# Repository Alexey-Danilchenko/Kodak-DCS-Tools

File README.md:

# Firmwares, Tools and sources to explore Kodak DCS cameras

This project contain the sources of all the tools produced as a result of my explorations of Kodak's DCS cameras: their internals, firmware, sensors, remaps, profile extraction etc. Quite a few of the tools are in aid of reverse engineering the firmwares and others are the results of those explorations.

I have mostly concentrated on Kodak ProBack 645M/C/H and SLRs Kodak DCS 14n, SLR/n, SLR/c models but a few of the tools are generic enough and may be applicable to other DCS cameras or standalone.

All software on this site is released free and under GPL license and in hope that it will be useful to other reverse engineers and Kodak camera explorers and users. 

The following is the list of topics:

* [Firmwares for Kodak cameras that I have build](Firmwares)
* [Camera profiles and profile extraction for Kodak cameras](profiles.md)
* [Software utilities (compiled versions of the sources above)](tools.md)
* [Mamiya/Phase One camera to digital back communication protocol](Mamiya_Protocol)
* [All the source code (defective pixels remap tools, IDA plugins, profile extraction, etc)](sources)
* [Sources of some of the code that I reverse engineered from firmwares and DSP](Firmwares/Reversed_Sources)
* [Kodak ProBack 645M/C/H hardware info - viewfinder masks, IR filters etc](hardware.md)
* [ProBack LCD upgrade to LED backlighting - daylight visible](Hardware/ProBack_LED_backlight)

The details of some of these explorations are published [here](https://dalex-257.livejournal.com/).

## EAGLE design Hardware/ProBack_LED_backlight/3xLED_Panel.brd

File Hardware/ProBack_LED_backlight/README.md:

# ProBack screen upgrade to use LED backlighting

Proback is an old digital back using [Sanyo ALP230CCX LCD](Ref/ALP230CCX.pdf) with CCFL tube as backlighting (that was a technology back in 2001). The CCFL tube lights up the edge of the screen and light guide plate with diffusers and light boosting sheets providing a backlight. The backlighting achieved this way is ok to start with but as CCFL tube ages it gets very weak and in a strong daylight practically nothing can be seen on the LCD. Besides CCFL tubes have limited lifespan and cannot be replaced since it is hard to find the sourcereplacemnt of that size nowadays. The aim of this hardware project is a complete replacement of this backlighting system with LED board instead of CCFL tube driven from the same on/off signal as the main backlight. The goal of it is to make it more usable in direct sunlight. This is the end result:

## Project history

This project followed the footsteps of something similar already done [here (link in russian)](https://web.archive.org/web/20171017015512/http://wowcamera.info/viewtopic.php?f=18&t=815&sid=7ef8761ab0095eecd0e935a0096e5fdd&start=740) but does a properly designed LED light source with constant current control.

I have designed the LED boards originally for 3x SMD LEDs in 2835 packages to fit perefecly inside LCD outer casing instead of CCFL. However upon experimenting with that it appears that Sanyo LCD backlight construction uses a light guide plate with straight vertical pattern that may work with linear light source like CCFL tube but does not work well with just a few LEDs creating long vertical beams of light. Modern LCD light guide panels use diaginal pattern that scatter light more evenly. With this in mind I also designed board for 6x SMD LEDs more closely spaced - those will need to be driven at close to a half the rated current to have the same power usage and light output as the 3x LEDs.

The alternative to 6x LED board and direct replacement is to place 3x LED lights sideways to the edge of the light guide - that means the light source needs to be behind the LCD case and holes for the LEDs need to be drilled into metallic frame to allow this ([similar to this](https://web.archive.org/web/20171021101310if_/http://wowcamera.info/download/file.php?id=11161&sid=97ba8f0b739cfa263edd7aab8cd7707e) used in approach from the russian project linked above). The latter approach is more involved than simple drop-in light replacement as this whole LED boards were designed to be but may be better at providing more uniform lighting.

The LED driver board provides constant current source from 3.3V and can be adjusted for your LEDs (by calculating R2 values for your LEDs current and is R2 = 95 mV / LED current mA (also see a note on schematic with a few sample values). The driver board was intentionally designed to be very small to fit onto a free space on ProBack board close to LCD and backlight power source.

Current design was tested with Yuji LEDs [YJ-BC-2835L](https://www.yujiintl.com/bc-2835l-0-2w/) (20-24 lumens per LED at rated current - CRI95). You can also use any other LEDs in 2835 packaging - make sure they have low forward voltage (<3.3V) and not a very high current (typically around 60mA for CRI95). The [Lumileds White CRI95 LED](https://eu.mouser.com/ProductDetail/Lumileds/L128-5095HA35000B1?qs=W%2FMpXkg%252BdQ4dqd7YM%2FLVnw%3D%3D) (manufacturer part number L128-5095HA35000B1) seems to be an ideal exact alternative to Yuji LEDs that is widely available (hence it is also specified below in list of parts as alternative).

This is assembled driver and LED light source for 3x LEDs designed to go behind LCD frame:

This is assembled driver and LED light source look for 6x LEDs designed to go in place as direct replacement of CCFL tube:

And this is 6x LED light source installed in place of CCFL and powered with LCD off - this shows drawback of this type of lighting caused by the linear structure of light guide panel. It could be addressed by sourcing the replacement for light guide panel with diagonal etching pattern but I have not managed to find any suitable replacement just yet.

Even with the visible backlight pattern, this is far easier to install since it is essentially taking CCFL tube out and placing LED strip board in its place and requires no drilling and no modifications of LCD frame. The brightness here on photo was reduced in postprocessing to show the pattern - in reality the backlight is much brighter.

For the Yuji LEDs above, the board in examples uses regulated LED current of 35mA (with resistor values as selected in schematics and specified in parts list below). For a string of 6 LEDs it produces voltage of 17V (slightly less but that is highly dependent on LED variations). This gives overall power consumption of 595mW which is still slightly less than original CCFL light at 600mW yet it is substantially brighter.

For the 6x LED board of the Yuji LEDs above, I would not recommend to go for brighter than with LED current of 35mA (30..35mA is the ideal range) since it then gets too bright and beyond capabilities of the LCD itself to handle (black becomes too bright). So the resistor values in the list of parts section below reflect this. I personally ended up using 35mA current and it is just about right balance.

This is how it looks all connected and lit:

## What is provided

In this repository you can find Eagle CAD [schematics](LED_Driver_Separate.sch) and [board](LED_Driver_Separate.brd) for LED driver, [schematics](3xLED_Panel.sch) and [board](3xLED_Panel.brd) for 3x LED board and [schematics](6xLED_Panel.sch) and [board](6xLED_Panel.brd) for 6x LED board. I have tested both LED boards but ended up using 6x one as it required no modification to LCD assembly and is more compact.

Separately you can also find [list of parts](BOM.csv) as well.

Gerber files for all the boards are in [Gerbers](Gerbers) subfirectory and are produced for [PCBWay](https://www.pcbway.com/) specifications (they were the only ones I found who can produce LED boards at 3mm minimum width).

When ordering the boards, LED lights board should be finished in white and have a thickness of 1.6mm - this ensures precise fit into a frame and sitting very close to the light guide panel. Minimal board width in PCBWay is 3mm and it is exact size of the gap in LED aluminium frame - so the fit is very tight. I would recommend to file boards a bit to 2.9mm for slightly easier fit.

The driver board for aesthetic reason should be green (to match the main board) and be any thickness of up to 1.6mm - ideally I would choose 0.8mm.

## LCD disassembly and light replacement

LCD assembly in a metal frame is a sandwich consisting of LCD panel itself (1), light boosting sheet of material under it (2), then diffusion sheet of material (3), then light guide acrylic panel (4) with white reflective material behind it and CCFL tube on one of the sides. All of that is packed within a metal frame.

It is relatively straightforward to take apart - LCD panel could be pried apart from the frame via side slots with a small screwdriver. This is how it looks when it is taken away:

Take a note of the corner pointed to by red arrow - the light boosting sheet and diffusing sheet have one rounded corner that goes in only one way in the right bottom corner of the LCD assembly. Next, gently take away light boosting sheet (it has metal sheen on one side):

Then, gently take away diffusion sheet, again noting round corner and where it should go:

All the components here are numbered with their order in the assembly from the top starting with LCD panel.

Lastly, take the light guide assembly from the frame, peel off the CCFL tube with the little white reflective sleeve holding it and discard the tube. Cut off the parts of white sleeve that stick to the light guide panel, both top and bottom bits and stick them both back to the light guide panel (this is important to avoid light bleeds). See the photo above where sleeve was already cut off and both parts were put back on with indication of the top part.

Next, push the LCD light board into the metal frame (it should be pretty tight) as far as it can go:

After that, place all the components back in the reverse order: light guide panel (4), then diffusion sheet (3) noting round corner position, then light boosting sheet (2) noting round corner position and at last put in the LCD panel (1) and click it into place. The LCD assembly is now complete.

## Board attachment

The LED driver board is designed to go on the empty space of the last board connecting to LCD - that sits directly behind CF card slot in the assembled position. Solder two short insulated wires to LED driver board, postion it close to C15 and C21 capacitors and solder ground and + wires as shown on this photo:

Both C15 and C21 are connected in parallel so it really does not matter which one of them the wires are soldered to, but the sides of them: top one for GND and lower side for +3.3V. When soldered, plug in ProBack battery briefly to check backlight working. Then glue the LED driver board to the ProBack board. I used Sugru to attach the board to the main board and insulate the contacts (this is mainly to be able to detach the driver board should I ever need to replace it):

Then attach the LCD connector and put the LCD in place with the ProBack board on top. For added safety, loosely cover LED driver board by Capton tape:

Then assemble the ProBack and test it on camera in the field.

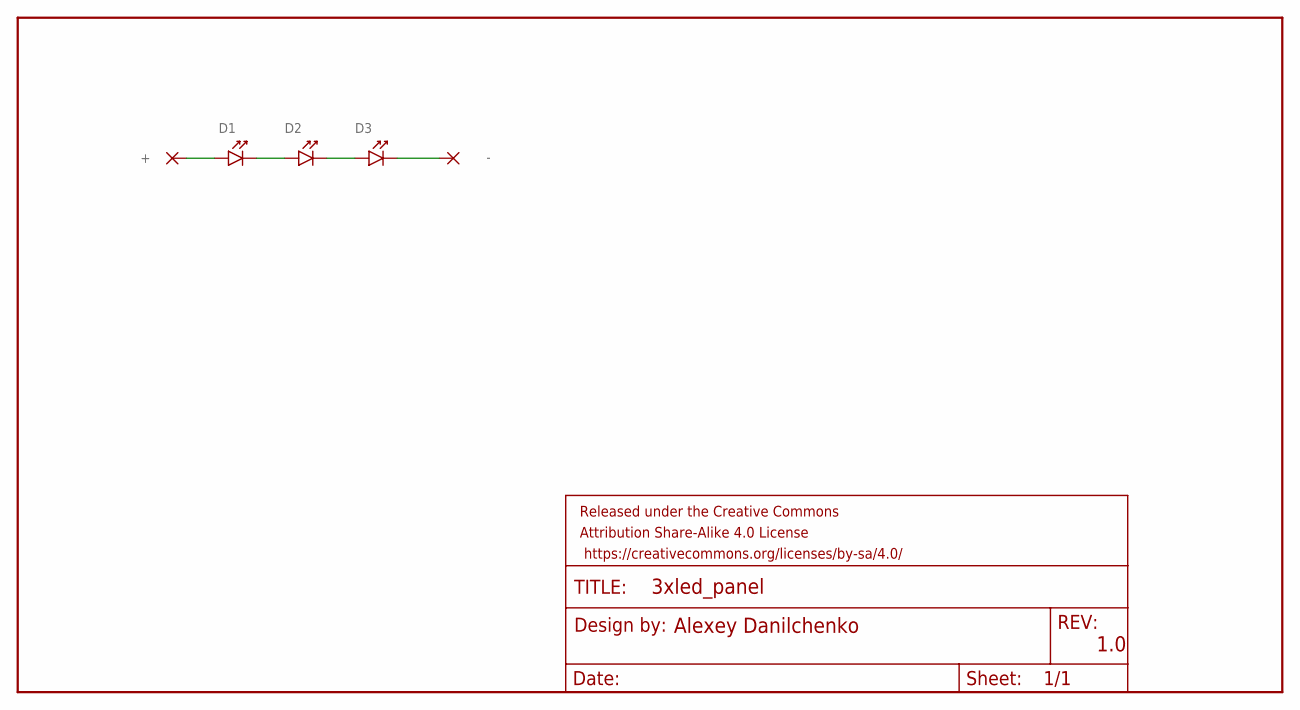
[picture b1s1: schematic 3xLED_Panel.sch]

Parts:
+: WIREPAD1,6/0,9; SMD3-2,15
-: SMD3X2.15; SMD3-2,15
D1, D2, D3: YUJI_2835_SMD; 2835_SMD
FRAME1: FRAME-LEDGER; CREATIVE_COMMONS

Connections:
unnamed: D1.CATHODE, D2.ANODE
unnamed: +.1, D1.ANODE
unnamed: D2.CATHODE, D3.ANODE
unnamed: -.1, D3.CATHODE

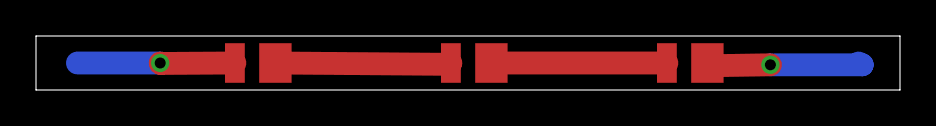
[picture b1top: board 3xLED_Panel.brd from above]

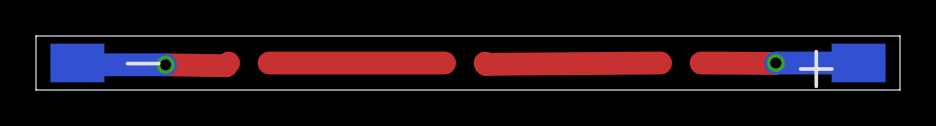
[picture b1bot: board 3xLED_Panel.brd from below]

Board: 2 copper layers, 48.0 x 3.0 mm, 6 parts (2 on the bottom side), 4 nets.

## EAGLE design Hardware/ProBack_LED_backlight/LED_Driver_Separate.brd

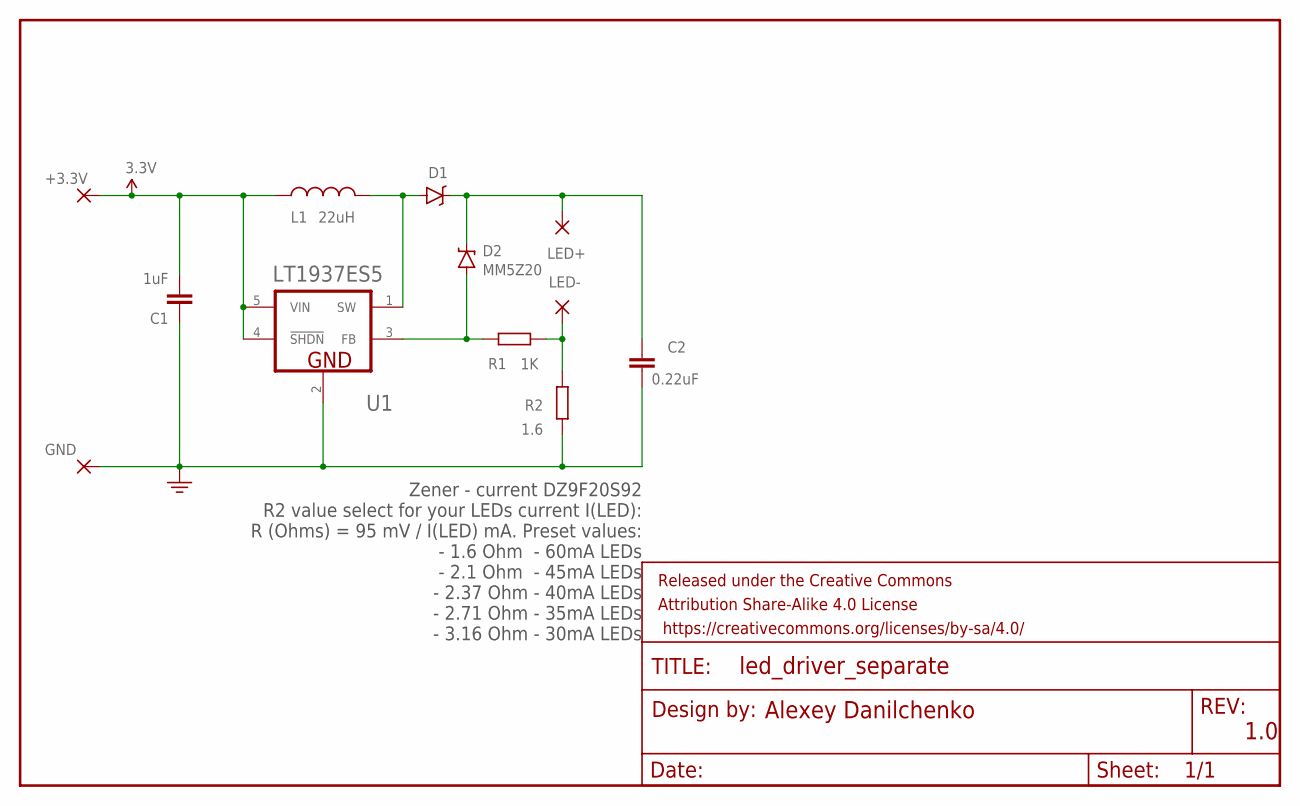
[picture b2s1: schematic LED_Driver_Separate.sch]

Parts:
+3.3V: SMD2X2; SMD2,54-2,54
C1: 1uF; C0805
C2: 0.22uF; 0603-CAP
D1: RB751; SOD-523
D2: MM5Z20; SOD-523
FRAME1: FRAME-LEDGER; CREATIVE_COMMONS
GND: SMD2X2; SMD2,54-2,54
L1: 22uH; 1210
LED+: SMD2X2; SMD2,54-2,54
LED-: SMD2X2; SMD2,54-2,54
R1: 1K; R0805
R2: 1.6; M1206
U1: LT1937ES5; LINEAR_TECHNOLOGY_LT1937ES5#TRMPBF_1

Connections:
3.3V: +3.3V.1, C1.1, L1.1, U1.4 (!SHDN!), U1.5 (VIN)
GND: C1.2, C2.2, GND.1, R2.1, U1.2 (GND)
unnamed: D1.A, L1.2, U1.1 (SW)
unnamed: D2.A, R1.2, U1.3 (FB)
unnamed: LED-.1, R1.1, R2.2
unnamed: C2.1, D1.C, D2.C, LED+.1

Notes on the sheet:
Zener - current DZ9F20S92 R2 value select for your LEDs current I(LED): R (Ohms) = 95 mV / I(LED) mA. Preset values: - 1.6 Ohm - 60mA LEDs - 2.1 Ohm - 45mA LEDs - 2.37 Ohm - 40mA LEDs - 2.71 Ohm - 35mA LEDs - 3.16 Ohm - 30mA LEDs
MM5Z20

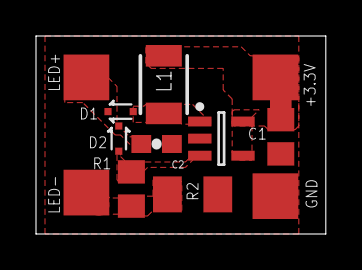
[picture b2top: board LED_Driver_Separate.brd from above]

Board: 2 copper layers, 16.1 x 11.0 mm, 13 parts (0 on the bottom side), 6 nets.

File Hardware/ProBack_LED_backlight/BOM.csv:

Part,Value,Package,Description,"Manufacturer product number, MPN",Manufacturer
C1,1uF,0805,"Capacitor X7R, 50V",CL21B105KBFNNNE,Samsung Electro-Mechanics
C2,0.22uF,0603,"Capacitor X7R, 50V",GCM188R71H224KA64D,Murata Electronics
D1,,SOD-523,Schottky diode,RB521S30T1G,ONSEMI
D2,,SOD-523,"Zener Diode, 20V, >0.1mA",BZT585B20T-7,Diodes Incorporated
L1,22uH,1210,Inductors,LQH32CN220K53L,Murata Electronics
R1,1K,0805,"Resistor, 1%",CRCW08051K00FKEA,Vishay Dale
R2,2.67,1206,High precision 0.1% resistor,CPF1206B2R67E1,TE Connectivity Passive Product
U1,,TSOT-23-5,"LED regulator from LT, TSOT-23 5pin package",LT1937ES5#TRMPBF,Linear Technologies
LEDS,,2835,YUJILEDS high CRI 2835 SMD,YJ-BC-2835L-G02,YUJILEDS

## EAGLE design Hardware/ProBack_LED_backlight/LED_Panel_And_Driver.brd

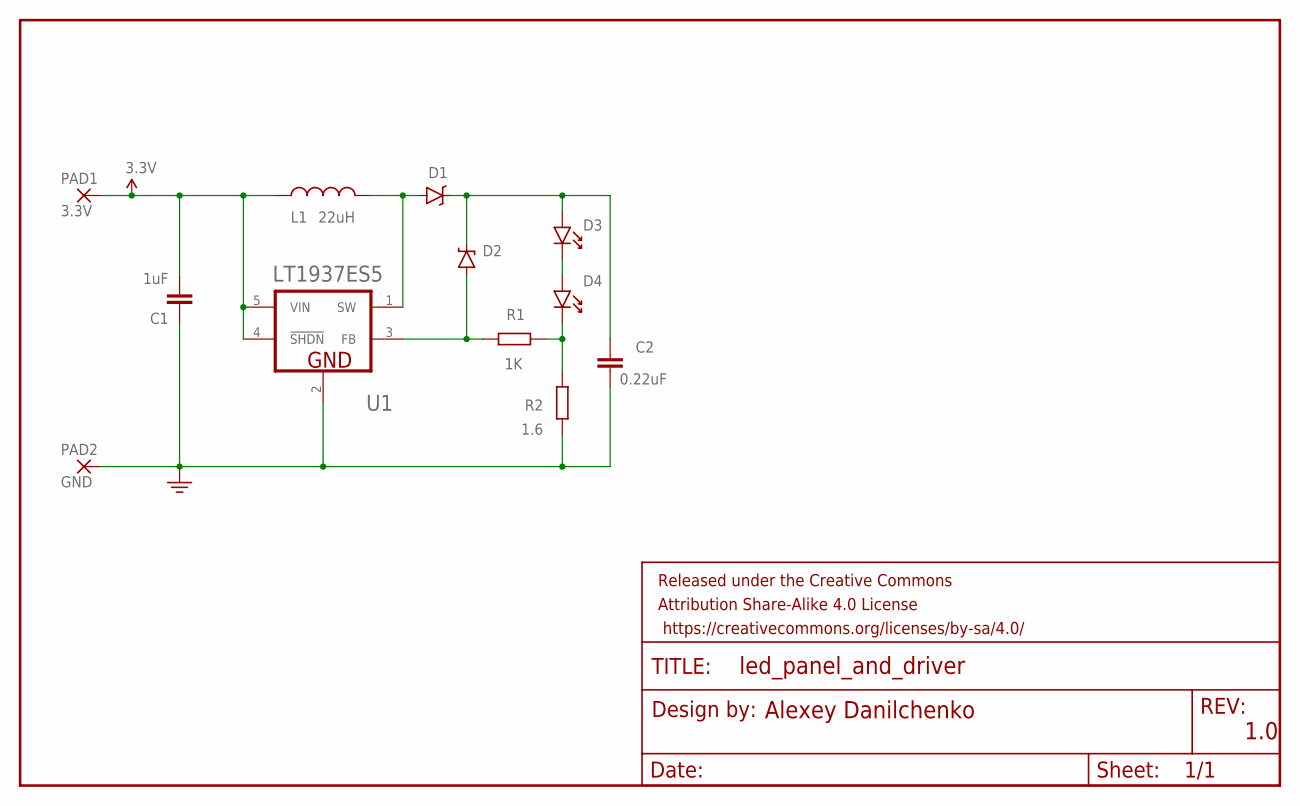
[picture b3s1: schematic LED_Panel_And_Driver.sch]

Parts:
C1: 1uF; C0805
C2: 0.22uF; 0603-CAP
D1: RB751; SOD-523
D2: DIODE-ZENER; SOD-923
D3, D4: YUJI_2835_SMD; 2835_SMD
FRAME1: FRAME-LEDGER; CREATIVE_COMMONS
L1: 22uH; 1210
PAD1: 3.3V; SMD2,54-5,08
PAD2: GND; SMD2,54-5,08
R1: 1K; R0805
R2: 1.6; M1206
U1: LT1937ES5; LINEAR_TECHNOLOGY_LT1937ES5#TRMPBF_1

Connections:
3.3V: C1.1, L1.1, PAD1.1, U1.4 (!SHDN!), U1.5 (VIN)
GND: C1.2, C2.2, PAD2.1, R2.1, U1.2 (GND)
unnamed: D1.A, L1.2, U1.1 (SW)
unnamed: D2.A, R1.2, U1.3 (FB)
unnamed: D3.CATHODE, D4.ANODE
unnamed: D4.CATHODE, R1.1, R2.2
unnamed: C2.1, D1.C, D2.C, D3.ANODE

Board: 2 copper layers, 13 parts (0 on the bottom side), 7 nets, no tracks yet.

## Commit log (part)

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2018-01-24 Initial submission
2018-01-24 Fixed README
2018-02-10 Added new firmware 3.4.4M
    This firmware fixes Proback for Mamiya synchronisation issues that goes back to original Kodak firmwares.
2018-02-10 Fixed images
2018-02-10 Updated links and descriptions in Firmwares section
2018-05-24 Documentation and minor updates
2018-05-24 Update a few messed up links
2018-05-24 Update formatting
2018-07-23 Fixed the spelling
2018-08-06 Added 3.4.5M and 3.4.5A.M firmwares
    Fixes some of the rare occurences of the broken capture that can occur in **Digital Combined** shutter mode when CCD sensor has not been reset. The fix essentially does not remove CCD activation imme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
2018-08-06 Correcting links and readme
2018-08-17 Fixed messed commit for 3.4.5 firmwares
    Somehow last commit picked up older firmware binaries and supporting files. This is fixed by this submission.
2020-12-06 DCSRemap updated to CMake build system
    Binaries for MacOS and Win54 are all rebuilt and updated as well to work on latest OS versions
2020-12-06 Fixed Windows min/max API clash
2020-12-22 Added initial ProBack LED Backlight designs and Gerbers
    These use high CRI98 Yuji LED providing colour accurate and bright LCD for ProBack 645
2020-12-29 Added link to common to aid restructuring
2021-01-04 Updated board
2021-01-04 Updated IDA source to cmake build system and IDA SDK v7.x (including prebuild versions for Windows and Mac)
2021-01-09 Made DSP CPU module off by default
    This module is a patch to IDA SDK one so needs extra steps hence disabled by default
2021-01-11 Added common link
2021-01-11 Firmware plugin updated to compile with CMake and to work with Double Commander (MacOS as well)
2021-01-11 Replaced tabs with spaces
2021-01-20 PPC .sbss segment symbols added to enum
    IDA Pro PowerPC decompiler cannot handle short addressing in .sbss segment properly. To make source code readable added all sbss symbols to SBSS_SYMBOL enum that can be used in decompiler sources
2021-01-20 Extended PPC symbols enum for all short symbols (addresses < 0x7FFF)
2021-05-15 Extended dates for Proback and Proback+ to 2099 (firmware 3.2.10)
2021-05-16 Got rid of dead end firmware, 3.2.10 is now service enabled and date extended to 2099
2021-05-27 Updated firmware links
2021-11-24 Firmware 3.2.11
    Changed Battery Save Onset to allow time interval start from 1 min
2023-06-23 Updated board layout a bit
2023-06-24 Update boards and schematic
2023-06-24 Updated readmes
2023-06-30 Updated schematic and boards
2023-06-30 Updates to LED backlight
2023-06-30 Updated for PCBWay of doing boards
2023-07-01 Update description
2023-07-10 More details added
2023-07-10 Fixing typos
2023-07-10 Updated images
2023-07-13 LED backlight completed
2023-07-13 Final update
2023-07-13 Added more details and BOMs
2023-07-14 Small updates
2023-07-14 Readme update
2023-07-15 Updates on LED currents
2023-07-15 Added indication of the light guide sleave on the photo
2023-07-15 Correct spelling
2023-07-15 Added alternative LEDs
2024-05-15 Fixed ICC profile incompatibility with RPP, added variable gamma option for Iridient Developer
    Iridient developer needs linear profile or lesser gamma so both of those are supported now. ICC profiles should work correctly in RPP under latest MacOS now
2025-04-22 Update hardware.md
    Link to knight optical updated
2026-04-01 QT6 and Apple Silicon support
    Updated to QT6 and with support for Apple Silicon Mac. English language only. No functional changes otherwise
2026-04-01 Update dependencies

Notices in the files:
parts and their libraries:
SparkFun-Aesthetics: Licensing: Creative Commons ShareAlike 4.0 International - https://creativecommons.org/licenses/by-sa/4.0
SparkFun-Aesthetics: Released under the Creative Commons
SparkFun-Aesthetics: https://creativecommons.org/licenses/by-sa/4.0
